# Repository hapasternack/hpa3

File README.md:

Copyright (c) 2020-2025 Henry A. Pasternack.  All rights reserved.

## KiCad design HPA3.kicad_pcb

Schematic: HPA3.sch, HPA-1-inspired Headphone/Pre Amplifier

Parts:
C1, C2, C7, C9, C10, C12, C13, C18, C20, C21: 100nF; C_Rect_L7.2mm_W2.5mm_P5.00mm_FKS2_FKP2_MKS2_MKP2
C3, C11, C14, C22: 220uF; CP_Radial_D10.0mm_P5.00mm
C4, C15: 330pF; C_Disc_D5.0mm_W2.5mm_P5.00mm
C5, C6, C16, C17: 1uF; C_Rect_L7.2mm_W5.5mm_P5.00mm_FKS2_FKP2_MKS2_MKP2
C8, C19: 10nF; C_Rect_L7.2mm_W3.0mm_P5.00mm_FKS2_FKP2_MKS2_MKP2
C23: 100uF; CP_Elec_5x5.8
C24: 0.1uF; C_1206_3216Metric_Pad1.42x1.75mm_HandSolder
D1: 1N914; D_DO-35_SOD27_P7.62mm_Horizontal
D2: D_Zener; D_1206_3216Metric_Pad1.42x1.75mm_HandSolder
J1, J7: Servo; PinHeader_1x02_P2.54mm_Vertical
J2, J8, J12: Conn_01x02; Molex-22-11-2022-2-Pin-Header
J3: PWR R; Molex-41791-0850-3-Pin-Header
J4, J5: Conn_01x02; Molex-41791-0849-2-Pin-Header
J6: Conn_01x03; Molex-22-11-2032-3-Pin-Header
J9: PWR L; Molex-41791-0850-3-Pin-Header
J10, J11: Conn_01x01_Male; 1-pad-wire-connector-22-ga
K1: G6H-2; Relay_DPDT_Omron_G6H-2
P1, P3: 1K; Potentiometer_Bourns_3296Y_Vertical
P2, P4: 500; Potentiometer_Bourns_3296Y_Vertical
Q1, Q2, Q9, Q14, Q15, Q22: BC560C; TO-92_Inline
Q3, Q16: KSA992; TO-92_Inline
Q4, Q17: FQP3N30; TO-220-3_Horizontal_TabDown
Q5, Q6, Q12, Q13, Q18, Q19, Q25, Q26: BC550C; TO-92_Inline
Q7, Q20: 2SK170BL; TO-92_Inline
Q8, Q21: 2SJ74BL; TO-92_Inline
Q10, Q23: FQP3P20; TO-220-3_Horizontal_TabDown
Q11, Q24: KSC1845; TO-92_Inline
Q27, Q28, Q30: MMBT3906; SOT-23
Q29: MMBT3904; SOT-23
R1, R18, R29, R46: 332; R_Axial_DIN0207_L6.3mm_D2.5mm_P10.16mm_Horizontal
R2, R28, R30, R56: 100; R_Axial_DIN0207_L6.3mm_D2.5mm_P10.16mm_Horizontal
R3, R27, R31, R55: 221; R_Axial_DIN0207_L6.3mm_D2.5mm_P10.16mm_Horizontal
R4, R23, R26, R32, R51, R54: 475; R_Axial_DIN0207_L6.3mm_D2.5mm_P10.16mm_Horizontal
R5, R25, R33, R53: 6K8; R_Axial_DIN0207_L6.3mm_D2.5mm_P10.16mm_Horizontal
R6, R9, R22, R24, R34, R37, R50, R52: 4K7; R_Axial_DIN0207_L6.3mm_D2.5mm_P10.16mm_Horizontal
R7, R35: 475K; R_Axial_DIN0207_L6.3mm_D2.5mm_P10.16mm_Horizontal
R8, R36: 10K; R_Axial_DIN0207_L6.3mm_D2.5mm_P10.16mm_Horizontal
R10, R21, R38, R49: 3R3 3W; R_Axial_DIN0411_L9.9mm_D3.6mm_P12.70mm_Horizontal
R11, R39: 150K; R_Axial_DIN0207_L6.3mm_D2.5mm_P10.16mm_Horizontal
R12, R40: 1M; R_Axial_DIN0207_L6.3mm_D2.5mm_P10.16mm_Horizontal
R13, R17, R41, R45: 22; R_Axial_DIN0207_L6.3mm_D2.5mm_P10.16mm_Horizontal
R14, R42: 1K; R_Axial_DIN0207_L6.3mm_D2.5mm_P10.16mm_Horizontal
R15, R43: 681; R_Axial_DIN0207_L6.3mm_D2.5mm_P10.16mm_Horizontal
R16, R44: 0R47 3W; R_Axial_DIN0411_L9.9mm_D3.6mm_P12.70mm_Horizontal
R19, R47: 100K; R_Axial_DIN0207_L6.3mm_D2.5mm_P10.16mm_Horizontal
R20, R48: 47; R_Axial_DIN0207_L6.3mm_D2.5mm_P10.16mm_Horizontal
R57: 10R; R_Axial_DIN0207_L6.3mm_D2.5mm_P10.16mm_Horizontal
R58: 10; R_Axial_DIN0207_L6.3mm_D2.5mm_P10.16mm_Horizontal
R59: 22K; R_1206_3216Metric
R60, R61, R63, R66: 10K; R_1206_3216Metric
R62: 91K; R_1206_3216Metric
R64, R65: 2K; R_1206_3216Metric
U1, U2: OPA604; SOIC-8_3.9x4.9mm_P1.27mm
U3: LM555; SOIC-8_3.9x4.9mm_P1.27mm

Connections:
+24L: C12.1, C13.1, C14.1, J9.1, P3.1, P3.2, Q17.2, R29.1, R30.1, R33.1, U2.7 (v+)
+24R: C1.1, C2.1, C3.1, J3.3, P1.1, P1.2, Q4.2, R1.1, R2.1, R5.1, U1.7 (v+)
-24L: C20.2, C21.2, C22.2, J9.3, Q23.2, R53.2, R55.2, R56.2, U2.4 (v-)
-24R: C9.2, C10.2, C11.2, J3.1, Q10.2, R25.2, R27.2, R28.2, U1.4 (v-)
GND-L: C13.2, C14.2, C19.2, C21.1, C22.1, J5.1, J9.2, K1.2, R58.1
GND-R: C2.2, C3.2, C8.2, C10.1, C11.1, J3.2, J4.2, K1.9, R57.1
GNDREF-L: C12.2, C15.2, C18.2, C20.1, J8.2, J11.1, R34.2, R35.1, R37.2, R46.2, R47.2, R50.1, R52.1, R58.2
GNDREF-R: C1.2, C4.2, C7.2, C9.1, J2.1, J10.1, R6.2, R7.1, R9.2, R18.2, R19.2, R22.1, R24.1, R57.2
unnamed: C4.1, C6.1, Q3.2, Q6.1, R4.2, R6.1, R8.1
unnamed: C5.1, R7.2, U1.2 (-)
unnamed: C5.2, J1.2, U1.6
unnamed: C6.2, Q6.3, Q11.2, R23.2, R24.2, R26.2
unnamed: C7.1, R12.2, U1.3 (+)
unnamed: C8.1, R20.2
unnamed: C15.1, C17.1, Q16.2, Q19.1, R32.2, R34.1, R36.1
unnamed: C16.1, R35.2, U2.2 (-)
unnamed: C16.2, J7.2, U2.6
unnamed: C17.2, Q19.3, Q24.2, R51.2, R52.2, R54.2
unnamed: C18.1, R40.2, U2.3 (+)
unnamed: C19.1, R48.2
unnamed: C23.1, C24.1, D2.1, J12.1, Q27.2, R59.2, U3.4, U3.8
unnamed: C23.2, R62.1, U3.2, U3.6
unnamed: C24.2, D1.2, J6.2, J12.2, K1.10, Q29.2, R62.2, U3.1
unnamed: D1.1, K1.1, Q27.3
unnamed: D2.2, Q28.2, Q30.2
unnamed: J1.1, R11.2
unnamed: J2.2, R14.1
unnamed: J4.1, K1.8
unnamed: J5.2, K1.3
unnamed: J6.1, R64.1
unnamed: J6.3, R65.1
unnamed: J7.1, R39.2
unnamed: J8.1, R42.1
unnamed: K1.4, R40.1, R44.1, R48.1
unnamed: K1.7, R12.1, R16.1, R20.1
unnamed: P1.3, R3.1
unnamed: P2.1, P2.2, Q6.2, R8.2
unnamed: P2.3, R23.1
unnamed: P3.3, R31.1
unnamed: P4.1, P4.2, Q19.2, R36.2
unnamed: P4.3, R51.1
unnamed: Q1.1, Q3.3, Q5.1
unnamed: Q1.2, Q2.1, Q2.2, Q3.1
unnamed: Q1.3, R1.2, R3.2
unnamed: Q2.3, R2.2
unnamed: Q4.1, R4.1
unnamed: Q4.3, R10.1
unnamed: Q5.2, R5.2, R9.1
unnamed: Q5.3, Q7.1
unnamed: Q7.2, Q8.2, R14.2, R19.1
unnamed: Q7.3, R13.1
unnamed: Q8.1, Q9.3
unnamed: Q8.3, R17.2
unnamed: Q9.2, R22.2, R25.1
unnamed: Q10.1, R26.1
unnamed: Q10.3, R21.2
unnamed: Q11.1, Q12.2, Q13.1, Q13.2
unnamed: Q9.1, Q11.3, Q12.1
unnamed: Q12.3, R27.1
unnamed: Q13.3, R28.1
unnamed: Q14.1, Q16.3, Q18.1
unnamed: Q14.2, Q15.1, Q15.2, Q16.1
unnamed: Q14.3, R29.2, R31.2
unnamed: Q15.3, R30.2
unnamed: Q17.1, R32.1
unnamed: Q17.3, R38.1
unnamed: Q18.2, R33.2, R37.1
unnamed: Q18.3, Q20.1
unnamed: Q20.2, Q21.2, R42.2, R47.1
unnamed: Q20.3, R41.1
unnamed: Q21.1, Q22.3
unnamed: Q21.3, R45.2
unnamed: Q22.1, Q24.3, Q25.1
unnamed: Q22.2, R50.2, R53.1
unnamed: Q23.1, R54.1
unnamed: Q23.3, R49.2
unnamed: Q24.1, Q25.2, Q26.1, Q26.2
unnamed: Q25.3, R55.1
unnamed: Q26.3, R56.1
unnamed: Q27.1, R61.1
unnamed: Q28.1, R63.1
unnamed: Q28.3, R64.2
unnamed: Q29.1, R66.1
unnamed: Q29.3, R59.1, R61.2, R63.2
unnamed: Q30.1, R60.1
unnamed: Q30.3, R65.2
unnamed: R10.2, R15.1, R16.2, R21.1
unnamed: R11.1, R13.2, R15.2, R17.1, R18.1
unnamed: R38.2, R43.1, R44.2, R49.1
unnamed: R39.1, R41.2, R43.2, R45.1, R46.1
unnamed: R60.2, R66.2, U3.3

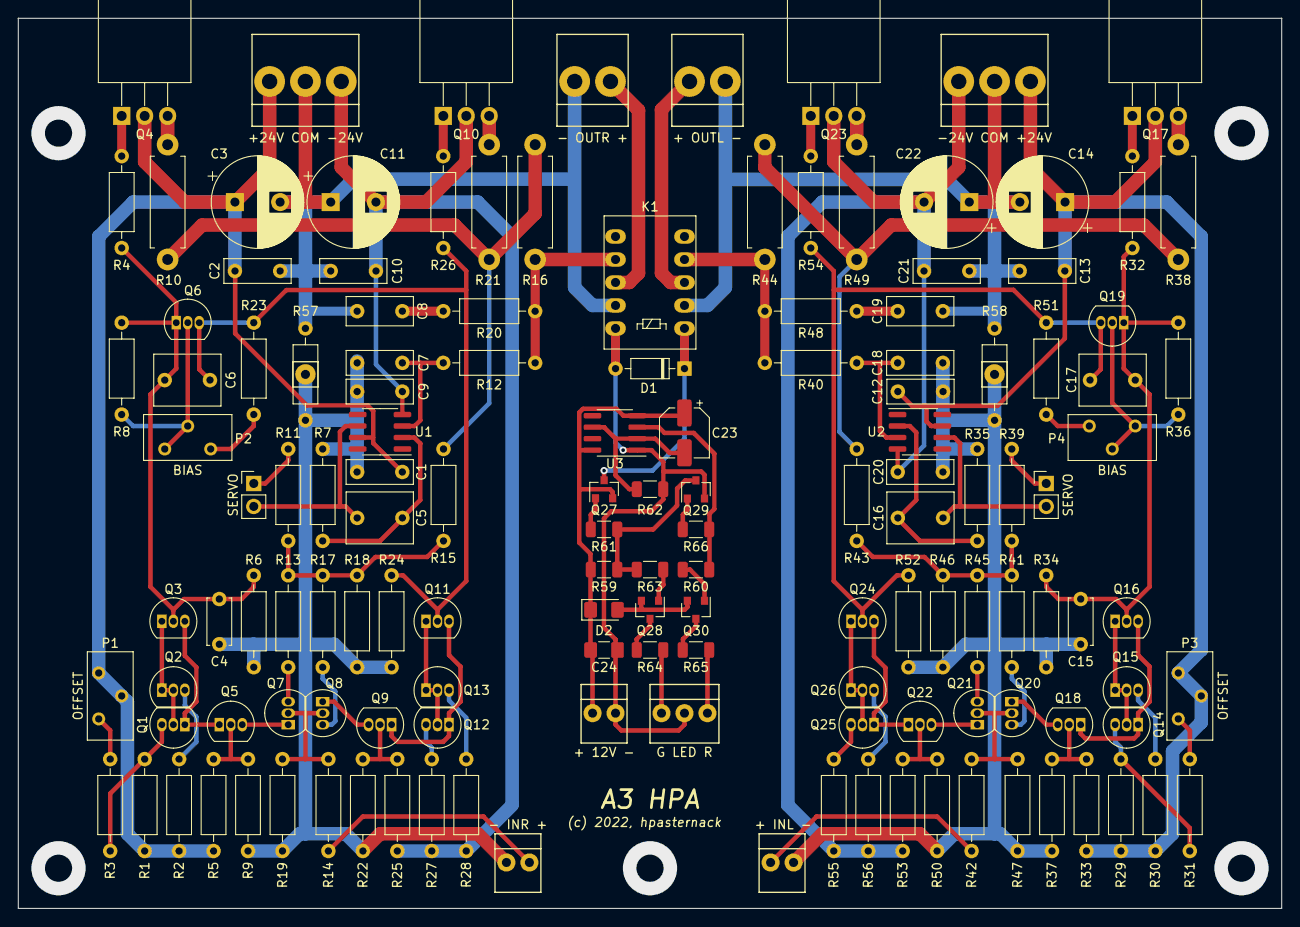
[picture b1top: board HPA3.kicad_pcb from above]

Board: 2 copper layers, 139.7 x 98.4 mm, 142 parts (0 on the bottom side), 91 nets.

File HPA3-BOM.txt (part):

"Ref"	"Value"	"Part"	"Footprint"	"Description"	"Vendor"
"C1"	"100nF"	"DIY-HPA-1-rescue:C_Small-device"	"Capacitor_THT:C_Rect_L7.2mm_W2.5mm_P5.00mm_FKS2_FKP2_MKS2_MKP2"	""	""
"C2"	"100nF"	"DIY-HPA-1-rescue:C_Small-device"	"Capacitor_THT:C_Rect_L7.2mm_W2.5mm_P5.00mm_FKS2_FKP2_MKS2_MKP2"	""	""
"C3"	"220uF"	"DIY-HPA-1-rescue:CP1_Small-device"	"Capacitor_THT:CP_Radial_D10.0mm_P5.00mm"	""	""
"C4"	"330pF"	"DIY-HPA-1-rescue:C_Small-device"	"Capacitor_THT:C_Disc_D5.0mm_W2.5mm_P5.00mm"	""	""
"C5"	"1uF"	"DIY-HPA-1-rescue:C_Small-device"	"Capacitor_THT:C_Rect_L7.2mm_W5.5mm_P5.00mm_FKS2_FKP2_MKS2_MKP2"	""	""
"C6"	"1uF"	"DIY-HPA-1-rescue:C_Small-device"	"Capacitor_THT:C_Rect_L7.2mm_W5.5mm_P5.00mm_FKS2_FKP2_MKS2_MKP2"	""	""
"C7"	"100nF"	"DIY-HPA-1-rescue:C_Small-device"	"Capacitor_THT:C_Rect_L7.2mm_W2.5mm_P5.00mm_FKS2_FKP2_MKS2_MKP2"	""	""
"C8"	"10nF"	"DIY-HPA-1-rescue:C_Small-device"	"Capacitor_THT:C_Rect_L7.2mm_W3.0mm_P5.00mm_FKS2_FKP2_MKS2_MKP2"	""	""
"C9"	"100nF"	"DIY-HPA-1-rescue:C_Small-device"	"Capacitor_THT:C_Rect_L7.2mm_W2.5mm_P5.00mm_FKS2_FKP2_MKS2_MKP2"	""	""
"C10"	"100nF"	"DIY-HPA-1-rescue:C_Small-device"	"Capacitor_THT:C_Rect_L7.2mm_W2.5mm_P5.00mm_FKS2_FKP2_MKS2_MKP2"	""	""
"C11"	"220uF"	"DIY-HPA-1-rescue:CP1_Small-device"	"Capacitor_THT:CP_Radial_D10.0mm_P5.00mm"	""	""
"C12"	"100nF"	"DIY-HPA-1-rescue:C_Small-device"	"Capacitor_THT:C_Rect_L7.2mm_W2.5mm_P5.00mm_FKS2_FKP2_MKS2_MKP2"	""	""
"C13"	"100nF"	"DIY-HPA-1-rescue:C_Small-device"	"Capacitor_THT:C_Rect_L7.2mm_W2.5mm_P5.00mm_FKS2_FKP2_MKS2_MKP2"	""	""
"C14"	"220uF"	"DIY-HPA-1-rescue:CP1_Small-device"	"Capacitor_THT:CP_Radial_D10.0mm_P5.00mm"	""	""
"C15"	"330pF"	"DIY-HPA-1-rescue:C_Small-device"	"Capacitor_THT:C_Disc_D5.0mm_W2.5mm_P5.00mm"	""	""
"C16"	"1uF"	"DIY-HPA-1-rescue:C_Small-device"	"Capacitor_THT:C_Rect_L7.2mm_W5.5mm_P5.00mm_FKS2_FKP2_MKS2_MKP2"	""	""
"C17"	"1uF"	"DIY-HPA-1-rescue:C_Small-device"	"Capacitor_THT:C_Rect_L7.2mm_W5.5mm_P5.00mm_FKS2_FKP2_MKS2_MKP2"	""	""
"C18"	"100nF"	"DIY-HPA-1-rescue:C_Small-device"	"Capacitor_THT:C_Rect_L7.2mm_W2.5mm_P5.00mm_FKS2_FKP2_MKS2_MKP2"	""	""
"C19"	"10nF"	"DIY-HPA-1-rescue:C_Small-device"	"Capacitor_THT:C_Rect_L7.2mm_W3.0mm_P5.00mm_FKS2_FKP2_MKS2_MKP2"	""	""
"C20"	"100nF"	"DIY-HPA-1-rescue:C_Small-device"	"Capacitor_THT:C_Rect_L7.2mm_W2.5mm_P5.00mm_FKS2_FKP2_MKS2_MKP2"	""	""
"C21"	"100nF"	"DIY-HPA-1-rescue:C_Small-device"	"Capacitor_THT:C_Rect_L7.2mm_W2.5mm_P5.00mm_FKS2_FKP2_MKS2_MKP2"	""	""
"C22"	"220uF"	"DIY-HPA-1-rescue:CP1_Small-device"	"Capacitor_THT:CP_Radial_D10.0mm_P5.00mm"	""	""
"C23"	"100uF"	"Device:CP1"	"Capacitor_SMD:CP_Elec_5x5.8"	"Polarized capacitor, US symbol"	""
"C24"	"0.1uF"	"Device:C"	"Capacitor_SMD:C_1206_3216Metric_Pad1.42x1.75mm_HandSolder"	"Unpolarized capacitor"	""
"D1"	"1N914"	"Diode:1N914"	"Diode_THT:D_DO-35_SOD27_P7.62mm_Horizontal"	"100V 0.3A Small Signal Fast Switching Diode, DO-35"	""
"D2"	"D_Zener"	"Device:D_Zener"	"Diode_SMD:D_1206_3216Metric_Pad1.42x1.75mm_HandSolder"	"Zener diode"	""
"J1"	"Servo"	"DIY-HPA-1-rescue:Jumper-device"	"Connector_PinHeader_2.54mm:PinHeader_1x02_P2.54mm_Vertical"	""	""
"J2"	"Conn_01x02"	"Connector_Generic:Conn_01x02"	"HP_Footprints:Molex-22-11-2022-2-Pin-Header"	"Generic connector, single row, 01x02, script generated (kicad-library-utils/schlib/autogen/connector/)"	""
"J3"	"PWR R"	"Connector_Generic:Conn_01x03"	"HP_Footprints:Molex-41791-0850-3-Pin-Header"	"Generic connector, single row, 01x03, script generated (kicad-library-utils/schlib/autogen/connector/)"	""
"J4"	"Conn_01x02"	"Connector_Generic:Conn_01x02"	"HP_Footprints:Molex-41791-0849-2-Pin-Header"	"Generic connector, single row, 01x02, script generated (kicad-library-utils/schlib/autogen/connector/)"	""
"J5"	"Conn_01x02"	"Connector_Generic:Conn_01x02"	"HP_Footprints:Molex-41791-0849-2-Pin-Header"	"Generic connector, single row, 01x02, script generated (kicad-library-utils/schlib/autogen/connector/)"	""
"J6"	"Conn_01x03"	"Connector_Generic:Conn_01x03"	"HP_Footprints:Molex-22-11-2032-3-Pin-Header"	"Generic connector, single row, 01x03, script generated (kicad-library-utils/schlib/autogen/connector/)"	""
"J7"	"Servo"	"DIY-HPA-1-rescue:Jumper-device"	"Connector_PinHeader_2.54mm:PinHeader_1x02_P2.54mm_Vertical"	""	""
"J8"	"Conn_01x02"	"Connector_Generic:Conn_01x02"	"HP_Footprints:Molex-22-11-2022-2-Pin-Header"	"Generic connector, single row, 01x02, script generated (kicad-library-utils/schlib/autogen/connector/)"	""
"J9"	"PWR L"	"Connector_Generic:Conn_01x03"	"HP_Footprints:Molex-41791-0850-3-Pin-Header"	"Generic connector, single row, 01x03, script generated (kicad-library-utils/schlib/autogen/connector/)"	""
"J10"	"Conn_01x01_Male"	"Connector:Conn_01x01_Male"	"HP_Footprints:1-pad-wire-connector-22-ga"	"Generic connector, single row, 01x01, script generated (kicad-library-utils/schlib/autogen/connector/)"	""
"J11"	"Conn_01x01_Male"	"Connector:Conn_01x01_Male"	"HP_Footprints:1-pad-wire-connector-22-ga"	"Generic connector, single row, 01x01, script generated (kicad-library-utils/schlib/autogen/connector/)"	""
"J12"	"Conn_01x02"	"Connector_Generic:Conn_01x02"	"HP_Footprints:Molex-22-11-2022-2-Pin-Header"	"Generic connector, single row, 01x02, script generated (kicad-library-utils/schlib/autogen/connector/)"	""
"K1"	"G6H-2"	"Relay:G6H-2"	"Relay_THT:Relay_DPDT_Omron_G6H-2"	"Omron Ultracompact, Ultrasensitive DPDT Relay, Single-side Stable"	""
"P1"	"1K"	"DIY-HPA-1-rescue:POT-device"	"Potentiometer_THT:Potentiometer_Bourns_3296Y_Vertical"	""	""
"P2"	"500"	"DIY-HPA-1-rescue:POT-device"	"Potentiometer_THT:Potentiometer_Bourns_3296Y_Vertical"	""	""
"P3"	"1K"	"DIY-HPA-1-rescue:POT-device"	"Potentiometer_THT:Potentiometer_Bourns_3296Y_Vertical"	""	""
"P4"	"500"	"DIY-HPA-1-rescue:POT-device"	"Potentiometer_THT:Potentiometer_Bourns_3296Y_Vertical"	""	""
"Q1"	"BC560C"	"Transistor_BJT:BC560"	"Package_TO_SOT_THT:TO-92_Inline"	"0.1A Ic, 45V Vce, PNP Small Signal Transistor, TO-92"	""
"Q2"	"BC560C"	"Transistor_BJT:BC560"	"Package_TO_SOT_THT:TO-92_Inline"	"0.1A Ic, 45V Vce, PNP Small Signal Transistor, TO-92"	""
"Q3"	"KSA992"	"Device:Q_PNP_ECB"	"Package_TO_SOT_THT:TO-92_Inline"	"PNP transistor, emitter/collector/base"	""
"Q4"	"FQP3N30"	"Device:Q_NMOS_GDS"	"Package_TO_SOT_THT:TO-220-3_Horizontal_TabDown"	"N-MOSFET transistor, gate/drain/source"	""
"Q5"	"BC550C"	"Transistor_BJT:BC550"	"Package_TO_SOT_THT:TO-92_Inline"	"0.1A Ic, 45V Vce, Small Signal NPN Transistor, TO-92"	""
"Q6"	"BC550C"	"Transistor_BJT:BC550"	"Package_TO_SOT_THT:TO-92_Inline"	"0.1A Ic, 45V Vce, Small Signal NPN Transistor, TO-92"	""
"Q7"	"2SK170BL"	"Device:Q_NJFET_DGS"	"Package_TO_SOT_THT:TO-92_Inline"	"N-JFET transistor, drain/gate/source"	""
"Q8"	"2SJ74BL"	"Device:Q_PJFET_DGS"	"Package_TO_SOT_THT:TO-92_Inline"	"P-JFET transistor, drain/gate/source"	""
"Q9"	"BC560C"	"Transistor_BJT:BC560"	"Package_TO_SOT_THT:TO-92_Inline"	"0.1A Ic, 45V Vce, PNP Small Signal Transistor, TO-92"	""
"Q10"	"FQP3P20"	"Device:Q_PMOS_GDS"	"Package_TO_SOT_THT:TO-220-3_Horizontal_TabDown"	"P-MOSFET transistor, gate/drain/source"	""
"Q11"	"KSC1845"	"Device:Q_NPN_ECB"	"Package_TO_SOT_THT:TO-92_Inline"	"NPN transistor, emitter/collector/base"	""
"Q12"	"BC550C"	"Transistor_BJT:BC550"	"Package_TO_SOT_THT:TO-92_Inline"	"0.1A Ic, 45V Vce, Small Signal NPN Transistor, TO-92"	""
"Q13"	"BC550C"	"Transistor_BJT:BC550"	"Package_TO_SOT_THT:TO-92_Inline"	"0.1A Ic, 45V Vce, Small Signal NPN Transistor, TO-92"	""
"Q14"	"BC560C"	"Transistor_BJT:BC560"	"Package_TO_SOT_THT:TO-92_Inline"	"0.1A Ic, 45V Vce, PNP Small Signal Transistor, TO-92"	""
"Q15"	"BC560C"	"Transistor_BJT:BC560"	"Package_TO_SOT_THT:TO-92_Inline"	"0.1A Ic, 45V Vce, PNP Small Signal Transistor, TO-92"	""
"Q16"	"KSA992"	"Device:Q_PNP_ECB"	"Package_TO_SOT_THT:TO-92_Inline"	"PNP transistor, emitter/collector/base"	""
"Q17"	"FQP3N30"	"Device:Q_NMOS_GDS"	"Package_TO_SOT_THT:TO-220-3_Horizontal_TabDown"	"N-MOSFET transistor, gate/drain/source"	""
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

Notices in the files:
HPA3.kicad_pcb:
(c) 2022, hpasternack
